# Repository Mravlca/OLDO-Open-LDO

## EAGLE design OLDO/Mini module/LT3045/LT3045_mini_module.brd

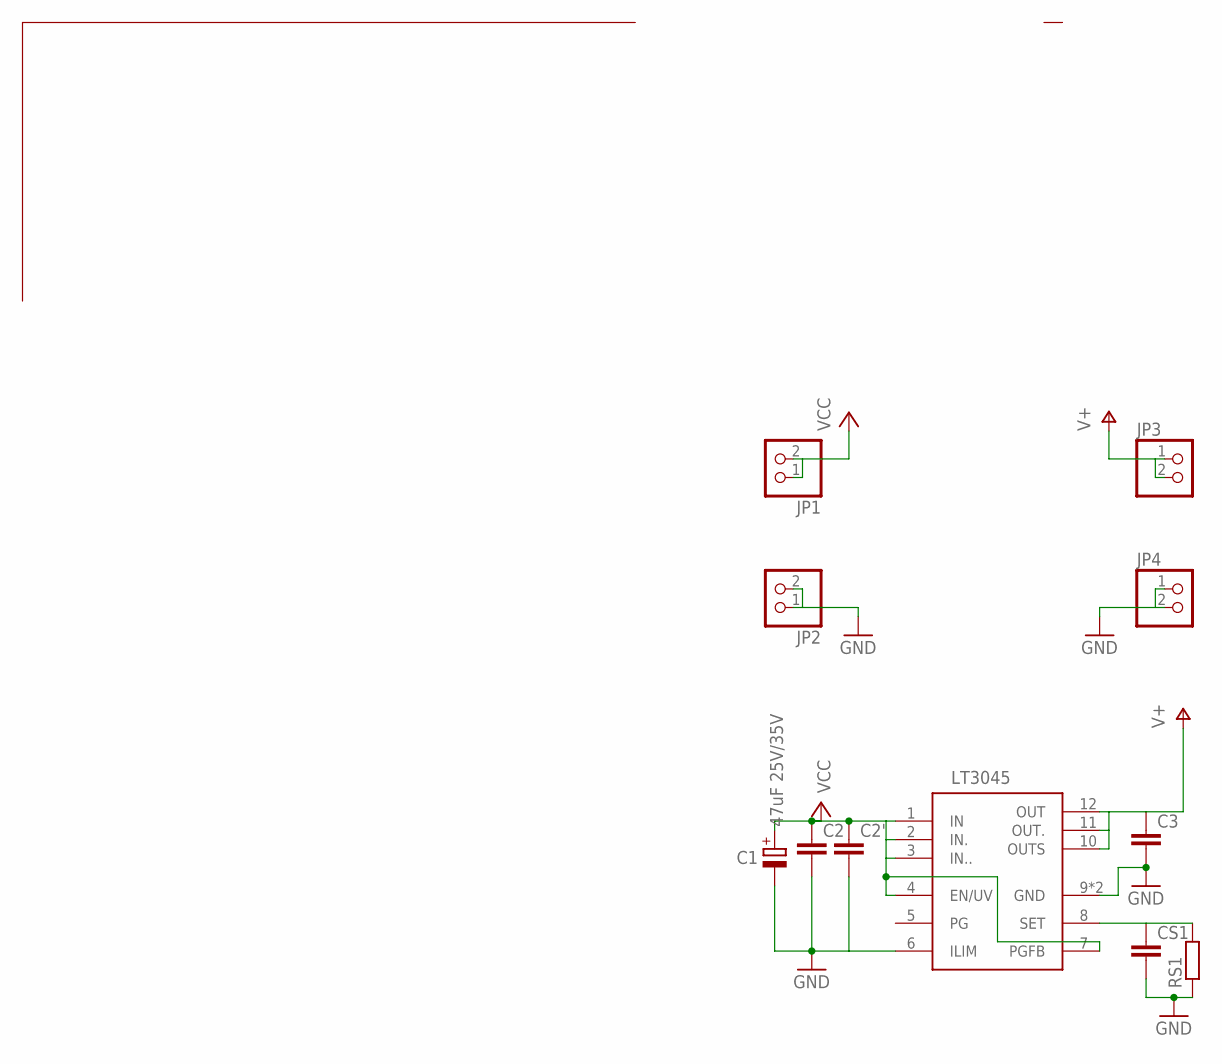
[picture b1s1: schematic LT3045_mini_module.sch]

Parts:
C1: 47uF 25V/35V; D/7343-31R
C2, C2', C3: C-EUC1206; C1206
CS1: C-EUC1206; C1206
JP1, JP2, JP3, JP4: PINHD-1X2; 1X02
RS1: R-EU_R1206; R1206
U1: LT3045; MSOP12

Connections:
GND: C1.-, C2.2, C2'.2, C3.2, CS1.2, JP2.1, JP2.2, JP4.1, JP4.2, RS1.1, U1.6 (ILIM), U1.9 (GND), U1.EXP (GND)
SET1: CS1.1, RS1.2, U1.8 (SET)
V+: C3.1, JP3.1, JP3.2, U1.10 (OUTS), U1.11 (OUT.), U1.12 (OUT)
VCC: C1.+, C2.1, C2'.1, JP1.1, JP1.2, U1.1 (IN), U1.2 (IN.), U1.3 (IN..), U1.4 (EN/UV), U1.7 (PGFB)

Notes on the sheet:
LT3045

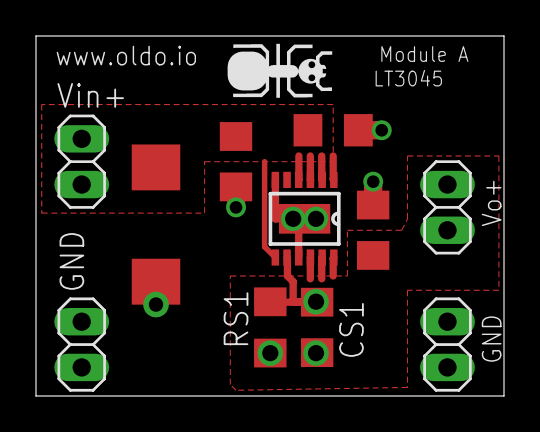
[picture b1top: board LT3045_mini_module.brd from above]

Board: 2 copper layers, 26.0 x 20.0 mm, 11 parts (0 on the bottom side), 4 nets.

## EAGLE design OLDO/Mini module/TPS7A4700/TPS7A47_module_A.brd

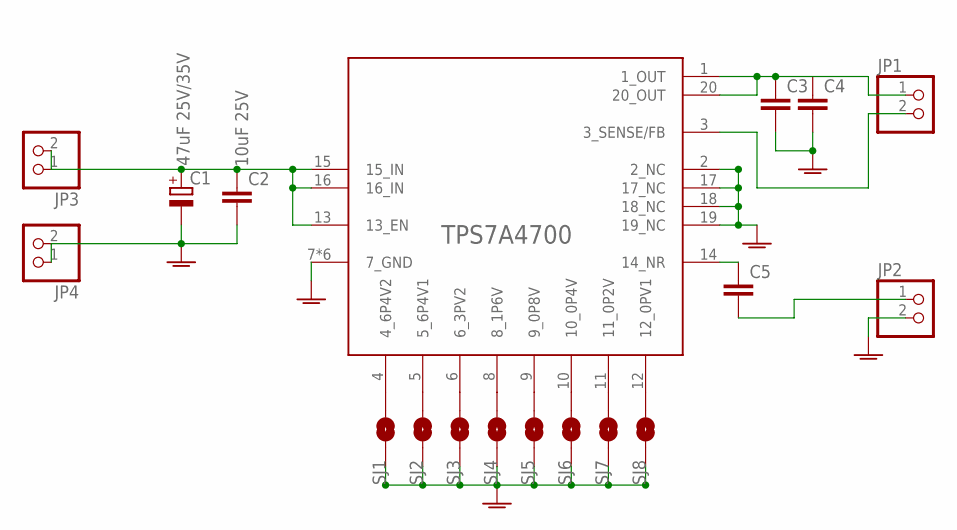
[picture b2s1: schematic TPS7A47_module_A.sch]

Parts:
C1: 47uF 25V/35V; D/7343-31R
C2: 10uF 25V; C0805K
C3, C4: C-EUC1206; C1206
C5: C-EUC0805; C0805
IC: TPS7A4701; VQFN20
JP1, JP2, JP3, JP4: PINHD-1X2; 1X02
SJ1, SJ2, SJ3, SJ4, SJ5, SJ6, SJ7, SJ8: SOLDERJUMPERNO; SJ_2S-NO

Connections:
GND: C1.-, C2.2, C3.2, C4.2, IC.2 (2_NC), IC.7 (7_GND), IC.17 (17_NC), IC.18 (18_NC), IC.19 (19_NC), IC.21 (7_GND), IC.P$1 (7_GND), IC.P$2 (7_GND), IC.P$3 (7_GND), IC.P$4 (7_GND), JP2.2, JP4.1, JP4.2, SJ1.1, SJ2.1, SJ3.1, SJ4.1, SJ5.1, SJ6.1, SJ7.1, SJ8.1
IN+: C1.+, C2.1, IC.13 (13_EN), IC.15 (15_IN), IC.16 (16_IN), JP3.1, JP3.2
unnamed: IC.4 (4_6P4V2), SJ1.2
unnamed: IC.5 (5_6P4V1), SJ2.2
unnamed: C5.2, JP2.1
unnamed: C5.1, IC.14 (14_NR)
unnamed: IC.6 (6_3PV2), SJ3.2
unnamed: IC.8 (8_1P6V), SJ4.2
unnamed: IC.9 (9_0P8V), SJ5.2
unnamed: IC.10 (10_0P4V), SJ6.2
unnamed: IC.11 (11_0P2V), SJ7.2
unnamed: IC.12 (12_0PV1), SJ8.2
unnamed: IC.3 (3_SENSE/FB), JP1.2
OUT+: C3.1, C4.1, IC.1 (1_OUT), IC.20 (20_OUT), JP1.1

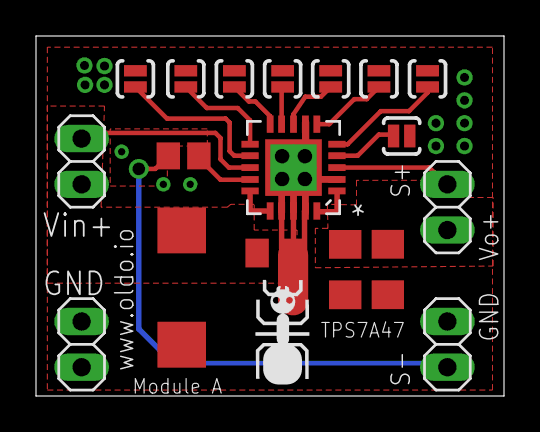
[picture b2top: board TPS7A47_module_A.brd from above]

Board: 2 copper layers, 26.0 x 20.0 mm, 18 parts (0 on the bottom side), 14 nets.

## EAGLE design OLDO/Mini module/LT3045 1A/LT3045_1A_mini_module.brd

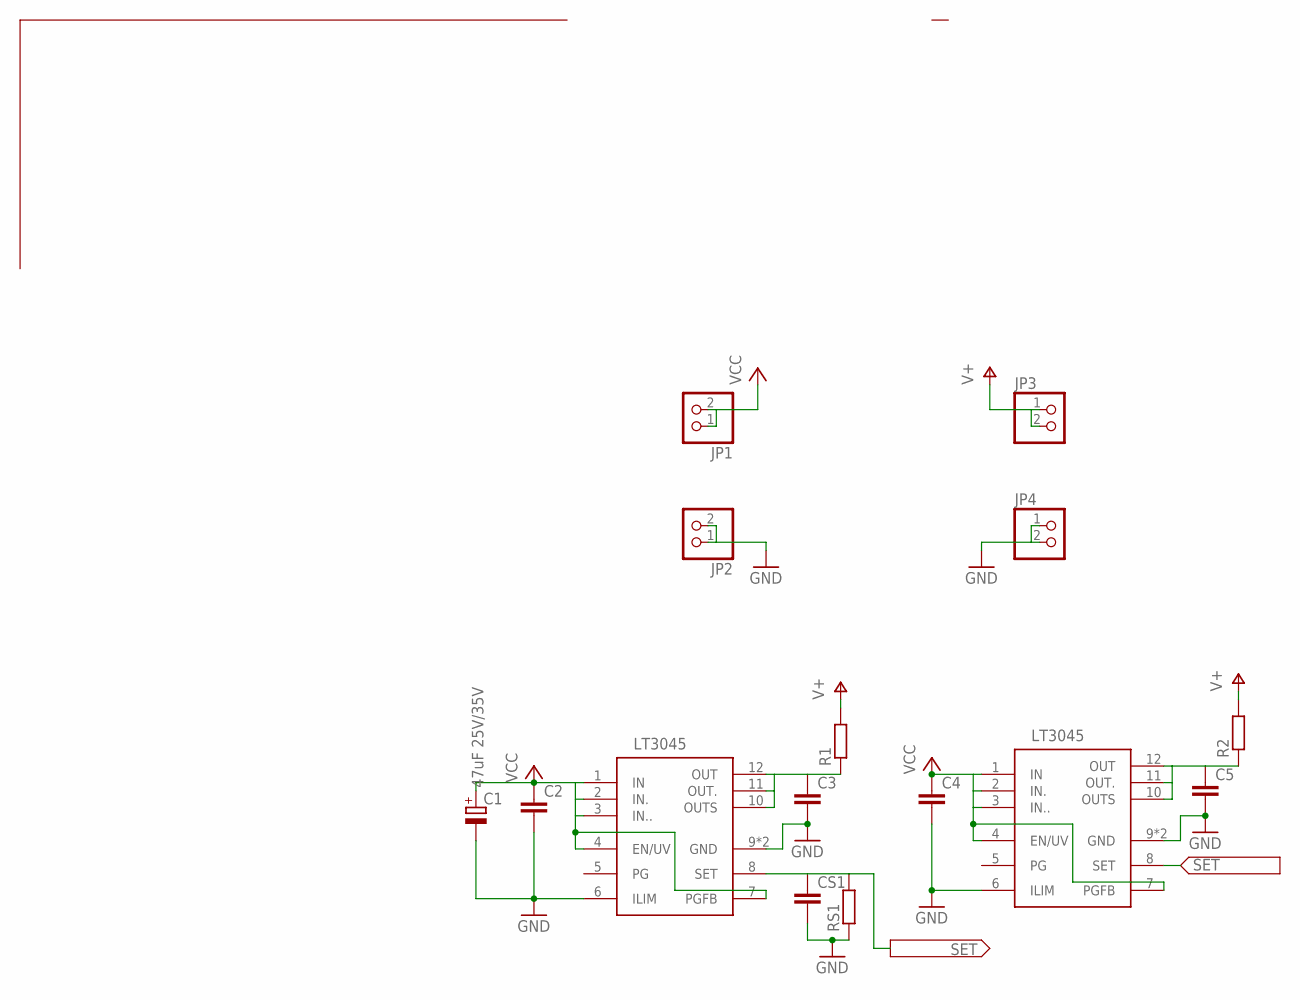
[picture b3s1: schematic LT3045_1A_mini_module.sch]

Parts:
C1: 47uF 25V/35V; D/7343-31R
C2, C3, C4, C5: C-EUC1206; C1206
CS1: C-EUC0805; C0805
JP1, JP2, JP3, JP4: PINHD-1X2; 1X02
R1, R2: R-EU_R0805; R0805
RS1: R-EU_R0805; R0805
U1, U2: LT3045; MSOP12

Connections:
GND: C1.-, C2.2, C3.2, C4.2, C5.2, CS1.2, JP2.1, JP2.2, JP4.1, JP4.2, RS1.1, U1.6 (ILIM), U1.9 (GND), U1.EXP (GND), U2.6 (ILIM), U2.9 (GND), U2.EXP (GND)
unnamed: C3.1, R1.1, U1.10 (OUTS), U1.11 (OUT.), U1.12 (OUT)
unnamed: C5.1, R2.1, U2.10 (OUTS), U2.11 (OUT.), U2.12 (OUT)
SET1: CS1.1, RS1.2, U1.8 (SET), U2.8 (SET)
V+: JP3.1, JP3.2, R1.2, R2.2
VCC: C1.+, C2.1, C4.1, JP1.1, JP1.2, U1.1 (IN), U1.2 (IN.), U1.3 (IN..), U1.4 (EN/UV), U1.7 (PGFB), U2.1 (IN), U2.2 (IN.), U2.3 (IN..), U2.4 (EN/UV), U2.7 (PGFB)

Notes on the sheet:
LT3045

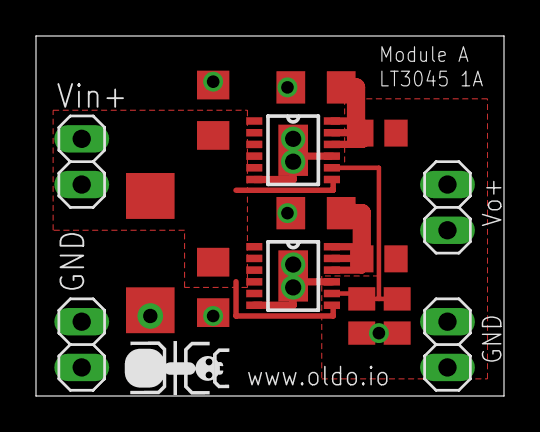
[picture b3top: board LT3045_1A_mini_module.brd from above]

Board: 2 copper layers, 26.0 x 20.0 mm, 15 parts (0 on the bottom side), 6 nets.

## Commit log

2017-03-03 Create readme2
2017-03-03 Create lt3045bom
2017-06-10 Create LT3045 1A
2017-06-10 Update LICENSE
2017-06-10 vcxvx
    cvx
2017-06-10 Create LT3045 1A BOM
2017-06-10 Create TPS7A4700 BOM
2017-06-10 Create LT3045 BOM
2017-06-10 Create Mini Module library
2017-06-10 Create Mini module lib

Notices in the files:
parts and their libraries:
sparkfun: Licensing: CC v3.0 Share-Alike You are welcome to use this library for commercial purposes.
